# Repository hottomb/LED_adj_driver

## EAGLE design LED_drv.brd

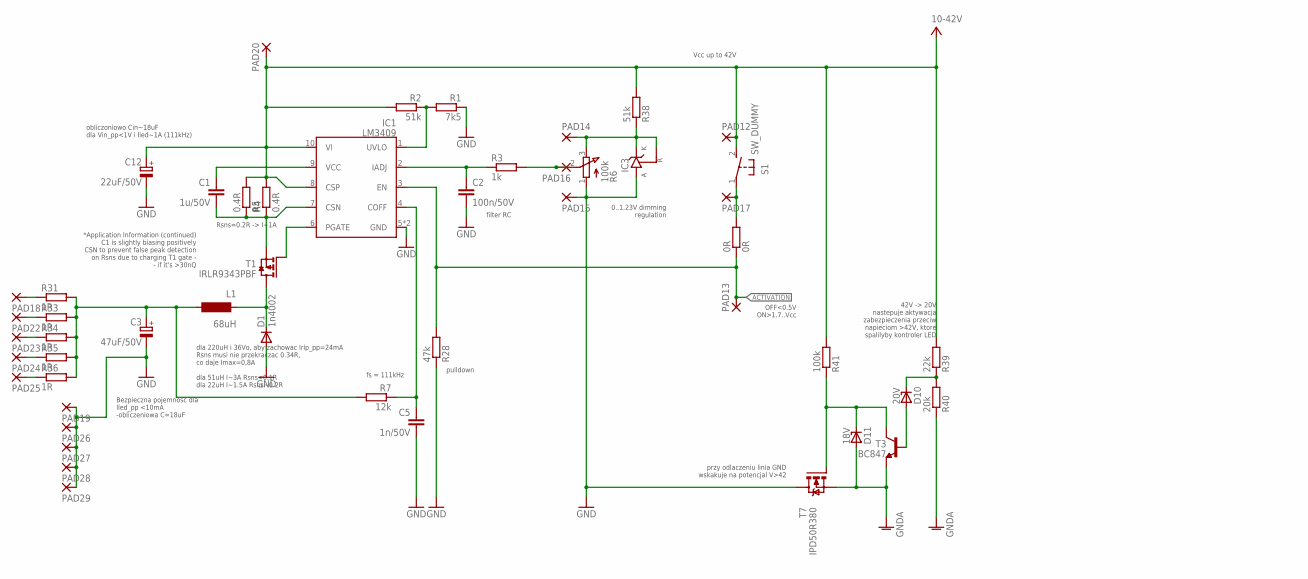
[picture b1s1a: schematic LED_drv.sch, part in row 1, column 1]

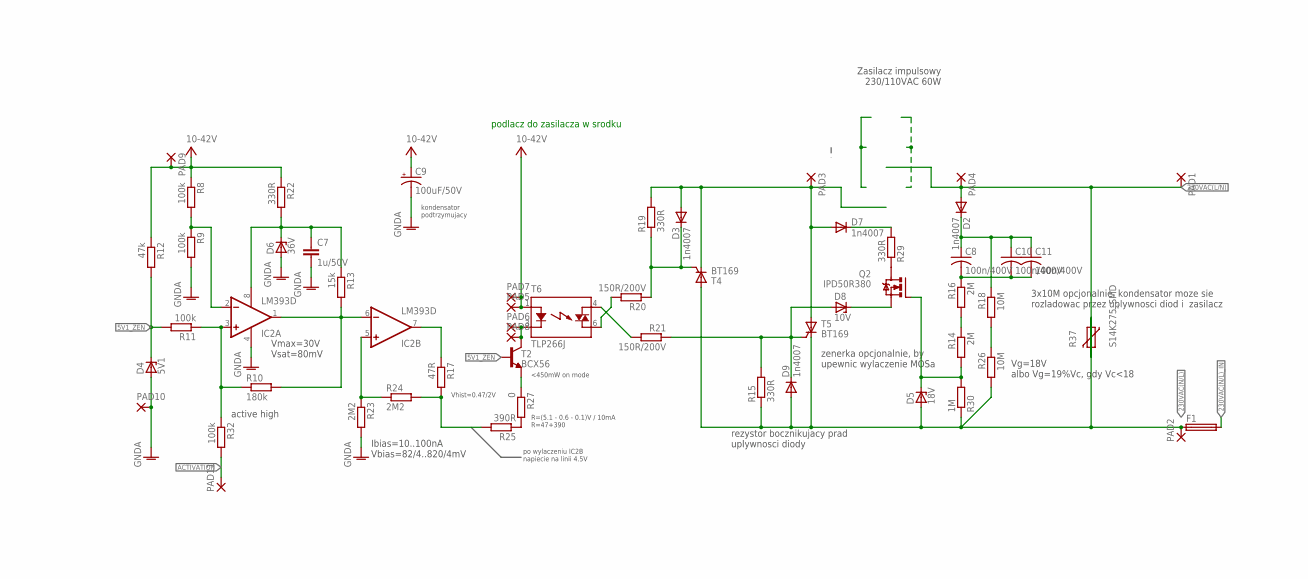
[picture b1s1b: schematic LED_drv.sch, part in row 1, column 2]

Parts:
0R: 0R; R1206
C1, C7: 1u/50V; C1206
C2: 100n/50V; C0805
C3: 47uF/50V; E5-6
C5: 1n/50V; C0603
C8, C10, C11: 100n/400V; C075-032X103
C9: 100uF/50V; E3,5-8
C12: 22uF/50V; E5-6
D1: 1n4002; DO214AC
D2, D3, D7, D9: 1n4007; DO-214AC
D4: 5V1; SOD80C
D5, D11: 18V; SOD80C
D6: 36V; SOD80C
D8: 10V; SOD80C
D10: 20V; SOD80C
F1: SH22,5A
IC1: LM3409; HVSSOP-10
IC2: LM393D; SO08
IC3: TL431-ASA; SOT23-3
L1: 68uH; CDRH104-R
PAD1, PAD2, PAD3, PAD4: SMD5; SMD2,54-5,08
PAD5, PAD6, PAD7, PAD8, PAD9, PAD10, PAD11, PAD12, PAD13, PAD14, PAD15, PAD16, PAD17, PAD18, PAD19, PAD20, PAD22, PAD23, PAD24, PAD25, PAD26, PAD27, PAD28, PAD29: SMD2; SMD1,27-2,54
Q2: IPD50R380; TO252-3-11
R1: 7k5; R1206
R2, R38: 51k; R1206
R3: 1k; R0805
R4, R5: 0.4R; R1206
R6: 100k; 3RP/1610N
R7: 12k; R1206
R8, R11, R32: 100k; R0805
R9, R41: 100k; R1206
R10: 180k; R1206
R12, R28: 47k; R0805
R13: 15k; R0805
R14, R16: 2M; R1206
R15, R19, R29: 330R; R1206
R17: 47R; R0805
R18, R26: 10M; R1206
R20, R21: 150R/200V; R1206
R22: 330R; R0805
R23, R24: 2M2; R0805
R25: 390R; R0805
R27: 0; R1206
R30: 1M; R1206
R31, R33, R34, R35, R36: 1R; R1206
R37: S14K275_SMD
R39: 22k; R1206
R40: 20k; R1206
S1: SW_DUMMY
T1: IRLR9343PBF; TO252-3-11
T2: BCX56; SOT89
T3: BC847; SOT23
T4, T5: BT169; SOT223
T6: TLP266J; SO6
T7: IPD50R380; TO252-3-11

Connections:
5V1_ZEN: D4.C, R11.2, R12.2, T2.B
230VAC(L/N): D2.A, PAD1.1, PAD4.1, R37.2
230VAC(N/L): D5.A, D9.A, F1.1, PAD2.1, R15.1, R26.2, R30.1, R37.1, T4.2 (A), T4.4 (A), T5.3 (C)
230VAC(N/L)_IN: F1.2
ACTIVATION: 0R.1, IC1.3 (EN), PAD11.1, PAD13.1, R28.2, R32.2
EER: IC2.3 (+IN), R10.1, R11.1, R32.1
GND: C2.2, C3.-, C5.2, C12.-, D1.A, IC1.5 (GND), IC1.EXT (GND), IC3.3 (A), PAD15.1, PAD19.1, PAD26.1, PAD27.1, PAD28.1, PAD29.1, R1.1, R6.1 (A), R28.1, T7.2 (D)
GNDA: C7.2, C9.-, D4.A, D6.A, D11.A, IC2.4 (V-), PAD10.1, R9.2, R23.2, R40.1, T3.2 (E), T7.3 (S)
unnamed: IC1.1 (UVLO), R1.2, R2.1
unnamed: D11.C, R41.1, T3.3 (C), T7.1 (G)
unnamed: C1.1, IC1.9 (VCC)
unnamed: C1.2, IC1.7 (CSN), R4.1, R5.1, T1.2 (S)
unnamed: C2.1, IC1.2 (IADJ), R3.1
unnamed: D1.C, L1.1, T1.3 (D)
unnamed: D5.C, Q2.1 (G), R14.2, R30.2
unnamed: PAD16.1, R3.2, R6.2 (S)
unnamed: IC1.6 (PGATE), T1.1 (G)
unnamed: 0R.2, PAD17.1, S1.1
unnamed: C3.+, L1.2, R7.2, R31.2, R33.2, R34.2, R35.2, R36.2
unnamed: R25.1, R27.2
unnamed: C5.1, IC1.4 (COFF), R7.1
unnamed: C8.1, C10.1, C11.1, D2.C, R18.1
unnamed: R14.1, R16.2
unnamed: R21.2, T6.4 (DS1)
unnamed: IC2.2 (-IN), R8.2, R9.1
unnamed: PAD22.1, R33.1
unnamed: IC2.5 (+IN), R23.1, R24.1
unnamed: R27.1, T2.E
unnamed: D3.C, R19.1, R20.1, T4.1 (G)
unnamed: D7.C, R29.2
unnamed: R20.2, T6.6 (DS2)
unnamed: R18.2, R26.1
unnamed: PAD6.1, PAD8.1, T2.C, T2.C@1 (C), T6.3 (K)
unnamed: IC2.7 (OUT), R17.1
unnamed: IC2.1 (OUT), IC2.6 (-IN), R10.2, R13.2
unnamed: R17.2, R24.2, R25.2
unnamed: C7.1, D6.C, IC2.8 (V+), R13.1, R22.2
unnamed: PAD18.1, R31.1
unnamed: D8.C, Q2.3 (S)
unnamed: C8.2, C10.2, C11.2, R16.1
unnamed: PAD23.1, R34.1
unnamed: PAD24.1, R35.1
unnamed: PAD25.1, R36.1
unnamed: Q2.2 (D), R29.1
unnamed: D8.A, D9.C, R15.2, R21.1, T5.1 (G)
unnamed: D10.C, R39.1, R40.2
unnamed: D10.A, T3.1 (B)
unnamed: IC3.1 (R), IC3.2 (K), PAD14.1, R6.3 (E), R38.1
NAH: D3.A, D7.A, PAD3.1, R19.2, T4.3 (C), T5.2 (A), T5.4 (A)
V+: C9.+, C12.+, IC1.8 (CSP), IC1.10 (VI), PAD5.1, PAD7.1, PAD9.1, PAD12.1, PAD20.1, R2.2, R4.2, R5.2, R8.1, R12.1, R22.1, R38.2, R39.2, R41.2, S1.2 (S), T6.1 (A)

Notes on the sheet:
*Application Information (continued) C1 is slightly biasing positively CSN to prevent false peak detection on Rsns due to charging T1 gate - - if it's >30nQ
Zasilacz impulsowy 230/110VAC 60W
Vg=18V albo Vg=19%Vc, gdy Vc<18
Vmax=30V Vsat=80mV
Ibias=10..100nA Vbias=82/4..820/4mV
R=(5.1 - 0.6 - 0.1)V / 10mA R=47+390
<450mW on mode
Vhist=0.47/2V
po wylaczeniu IC2B napiecie na linii 4.5V
kondensator podtrzymujacy
3x10M opcjonalnie, kondensator moze sie rozladowac przez uplywnosci diod i zasilacz
rezystor bocznikujacy prad uplywnosci diody
zenerka opcjonalnie, by upewnic wylaczenie MOSa
podlacz do zasilacza w srodku
active high
Vcc up to 42V
pulldown
0..1.23V dimming regulation
OFF<0.5V ON>1.7..Vcc
42V -> 20V nastepuje aktywacja zabezpieczenia przeciw napieciom >42V, ktore spalilyby kontroler LED
przy odlaczeniu linia GND wskakuje na potencjal V>42
filter RC
fs = 111kHz
dla 220uH i 36Vo, aby zachowac Irip_pp=24mA Rsns musi nie przekraczac 0.34R, co daje Imax=0,8A dla 51uH I~3A Rsns<0.1R dla 22uH I~1.5A Rsns~0.2R
Bezpieczna pojemnosc dla Iled_pp <10mA -obliczeniowa C=18uF
Rsns=0.2R -> I~1A
obliczoniowo Cin~18uF dla Vin_pp<1V i Iled~1A (111kHz)

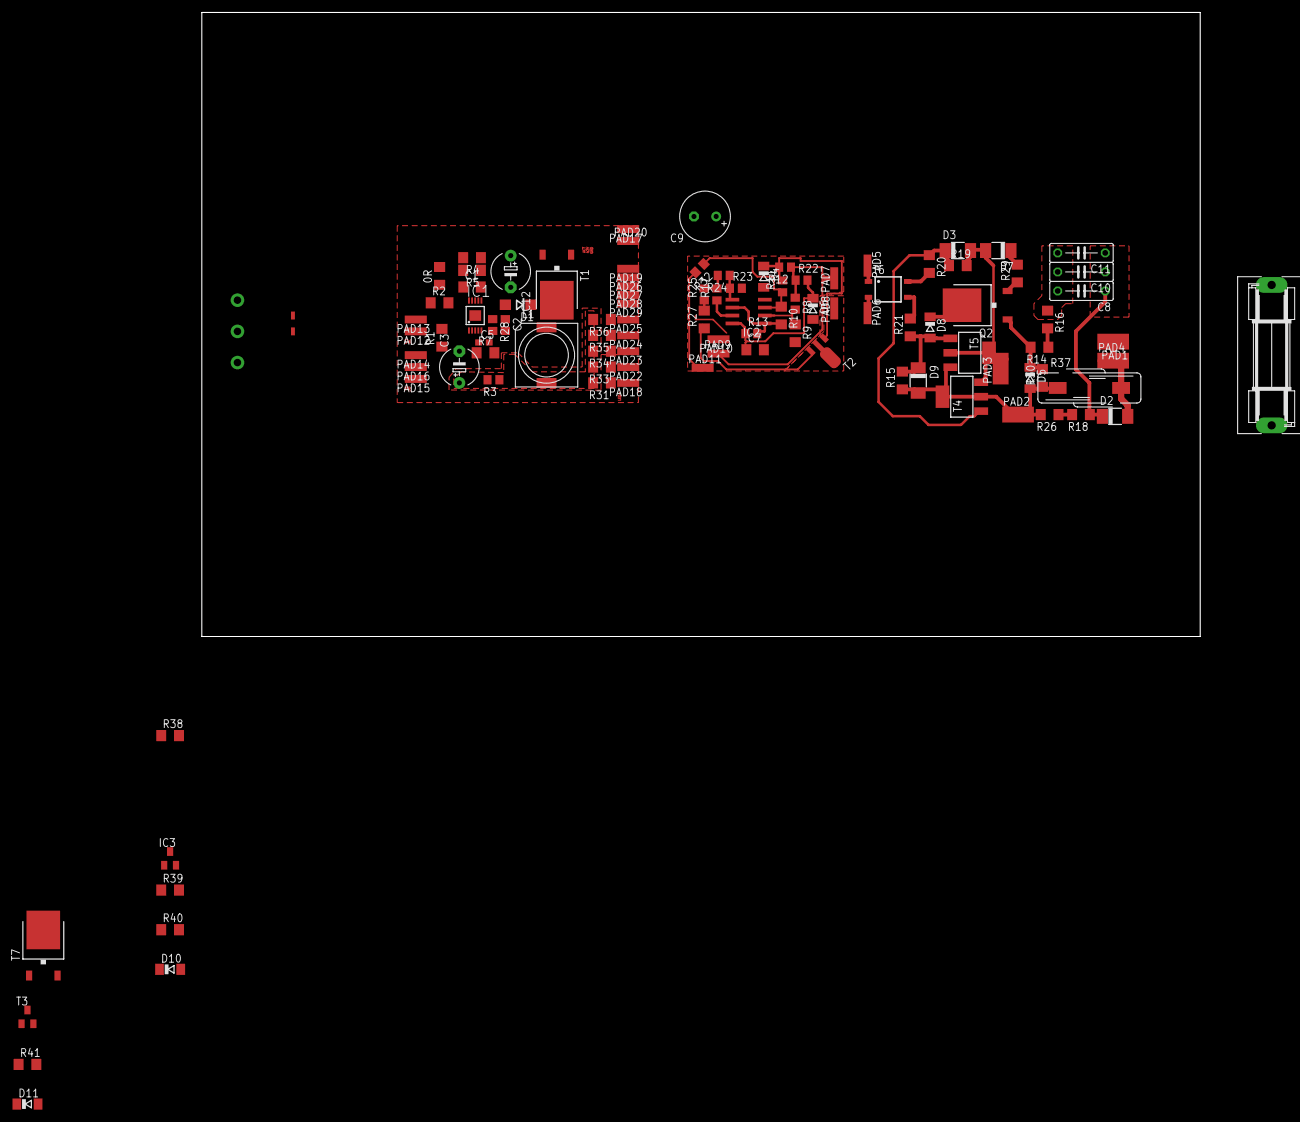
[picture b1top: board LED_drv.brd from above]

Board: 2 copper layers, 160.0 x 100.0 mm, 105 parts (1 on the bottom side), 49 nets.

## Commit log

2017-11-19 IC population
2017-12-01 Mains switch added
2017-12-01 Charge regeneration circuit
2017-12-03 Analog circuitry & switch correction
2017-12-03 Additional corrections
2017-12-05 Mains side PCB layout
2017-12-06 key side PCB layout
2017-12-19 PCB layout complete
2017-12-21 PCB layout complete
    minor update
2018-01-06 test_release
2018-08-27 screenshot added
    minor updates and comments
